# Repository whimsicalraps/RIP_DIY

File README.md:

# RIP DIY

Instructions: [Web](./rip_diy.md) & [PDF](./rip_diy.pdf)

PCB: [Base](https://oshpark.com/shared_projects/XV3uuEyj) & [Head](https://oshpark.com/shared_projects/YRoWpgCe)

BOM: [Octopart](https://octopart.com/bom-tool/D3BJBFqb)

Panel: [Illustrator File](https://github.com/whimsicalraps/MannequinsPanels)

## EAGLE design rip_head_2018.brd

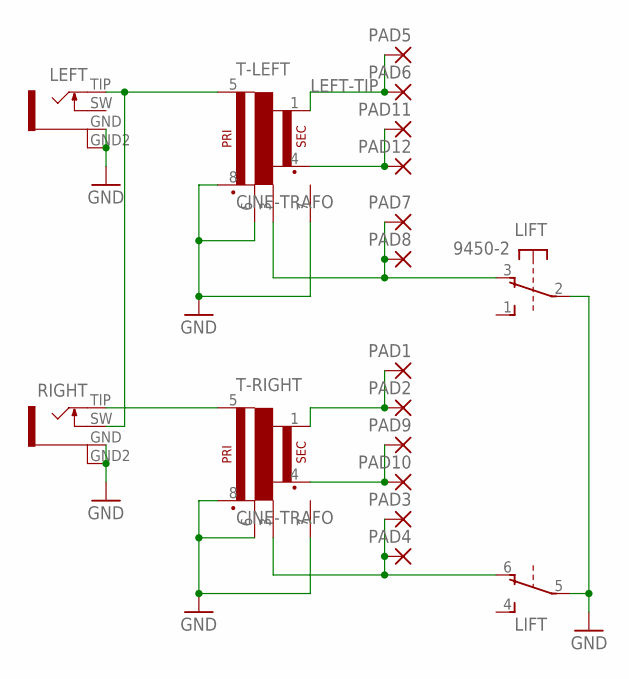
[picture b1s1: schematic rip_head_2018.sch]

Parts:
LEFT: SHAPES_PONY_ERTHENVAR-JACK; SHAPES_PONY_3.5MMJACK
LIFT: 9450-2
PAD1, PAD2, PAD3, PAD4, PAD5, PAD6, PAD7, PAD8, PAD9, PAD10, PAD11, PAD12: SMD2; SMD1,27-2,54
RIGHT: SHAPES_PONY_ERTHENVAR-JACK; SHAPES_PONY_3.5MMJACK
T-LEFT: CINE-TRAFO; CIRC-TRAFO
T-RIGHT: CINE-TRAFO; CIRC-TRAFO

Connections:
GND: LEFT.GND (1), LEFT.GND2 (4), LIFT.2, LIFT.5, RIGHT.GND (1), RIGHT.GND2 (4), T-LEFT.6 (C1), T-LEFT.7 (CASE), T-LEFT.8 (P2), T-RIGHT.6 (C1), T-RIGHT.7 (CASE), T-RIGHT.8 (P2)
LEFT-GND: LIFT.3 (O), PAD7.1, PAD8.1, T-LEFT.3 (C2)
LEFT-RING: PAD11.1, PAD12.1, T-LEFT.4 (S2)
LEFT-TIP: PAD5.1, PAD6.1, T-LEFT.1 (S1)
unnamed: RIGHT.TIP (2), T-RIGHT.5 (P1)
unnamed: LEFT.TIP (2), RIGHT.SW (3), T-LEFT.5 (P1)
RIGHT-GND: LIFT.6 (O), PAD3.1, PAD4.1, T-RIGHT.3 (C2)
RIGHT-RING: PAD9.1, PAD10.1, T-RIGHT.4 (S2)
RIGHT-TIP: PAD1.1, PAD2.1, T-RIGHT.1 (S1)

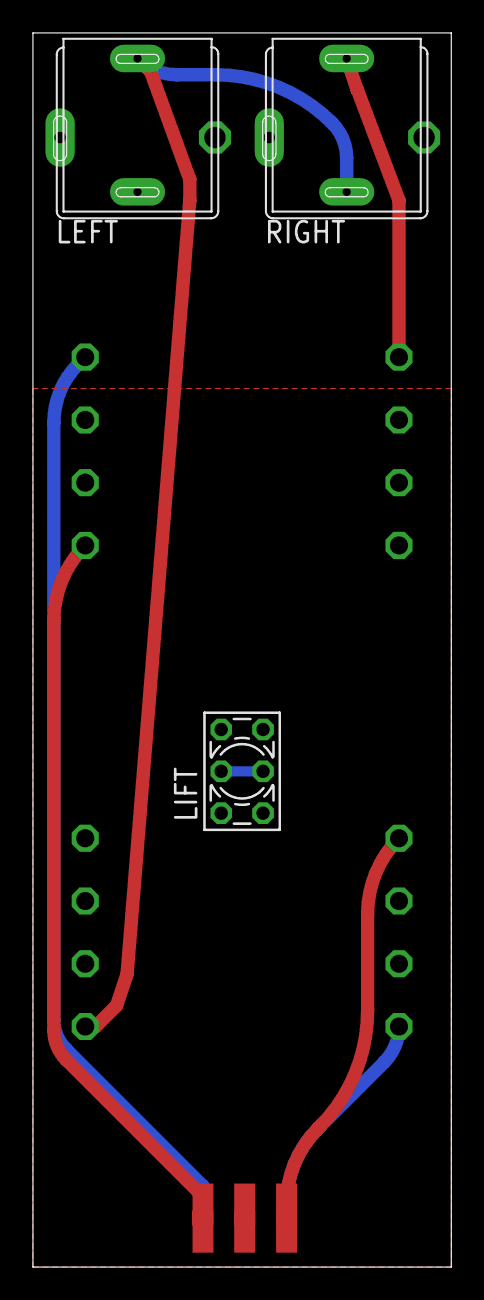
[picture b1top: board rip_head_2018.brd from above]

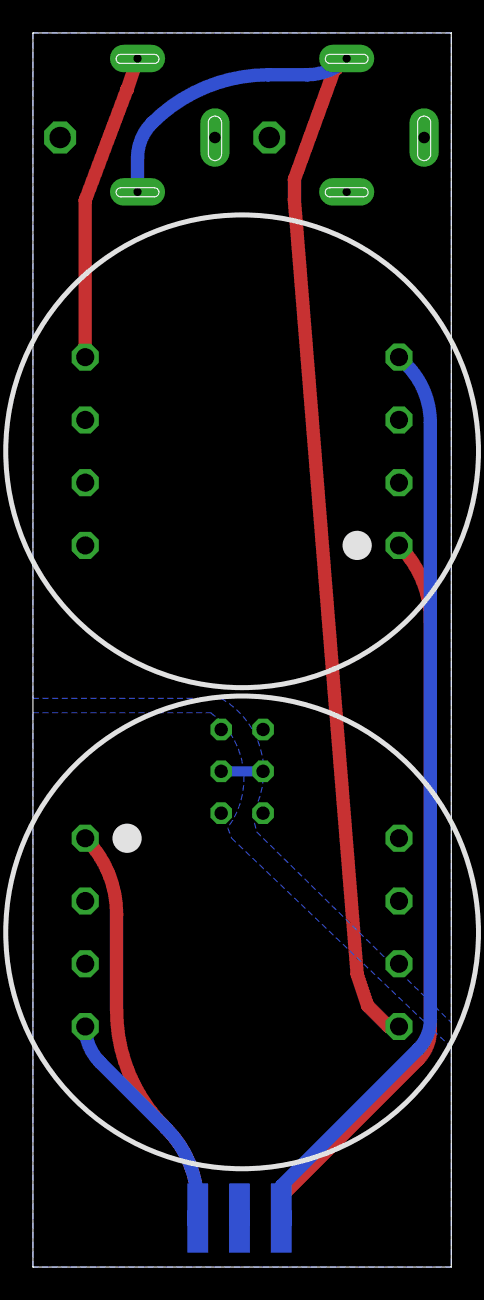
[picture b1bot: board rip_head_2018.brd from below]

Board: 2 copper layers, 25.4 x 74.9 mm, 17 parts (8 on the bottom side), 9 nets.

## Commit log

2019-07-02 create rip diy project.
2019-07-07 add eagle files
